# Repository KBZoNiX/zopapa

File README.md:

# Zopapa

A two-wheel differential-drive line-following robot: Arduino Nano firmware, an 8-channel reflectance sensor array, and two custom KiCad PCBs.

Full functional specification: [`docs/FSD.html`](docs/FSD.html) · User manual (Spanish): [`docs/MANUAL.html`](docs/MANUAL.html)

## Features

- PD line-following control loop (proportional + derivative, ~500 Hz)
- Relay-feedback (Åström–Hägglund) autotune — computes and installs new gains from an induced oscillation
- EEPROM persistence of tuned speed/gains and sensor calibration — no need to re-sweep the line sensor on every power-cycle
- Serial/Bluetooth command interface for live tuning and telemetry (shared UART, 9600 baud)
- Optional turbine/vacuum subsystem for extra downforce, ramped proportionally to steering correction
- On-board HMI: pushbutton (short press starts/stops; long press saves gains to EEPROM or recalibrates the sensor, depending on DIP 4 — see FSD §7.1), 4-position DIP bank, status LED, buzzer

## Repo layout

```
src/zopapa/       Arduino sketch (zopapa.ino is the entry point)
src/libraries/    Vendored first-party libraries: DRV8833 (motor driver), ATRSensors (line sensor)
hardware/         KiCad PCB projects — main_pcb (Rapiduino) and line_sensor_pcb (ATR-8A)
docs/FSD.html     Functional Specification Document
docs/MANUAL.html  User manual (Spanish) — physical controls and BT/Serial commands
```

## Build

Requires [arduino-cli](https://arduino.github.io/arduino-cli/) with the `arduino:avr` core installed.

```sh
arduino-cli compile --fqbn arduino:avr:nano --libraries src/libraries src/zopapa
```

Arduino IDE: open `src/zopapa/zopapa.ino` directly, and copy or symlink `src/libraries/*` into your sketchbook's `libraries/` folder first.

## Flash

Most Nano (and clone) boards need the old-bootloader CPU variant:

```sh
arduino-cli compile --fqbn arduino:avr:nano:cpu=atmega328old --libraries src/libraries -u -p /dev/ttyUSB0 src/zopapa
```

If uploads fail with repeated `not in sync` errors, that's this — try the `atmega328old` variant. Requires your account to be in the `dialout` group (Linux).

## Command interface

Sent over Serial or Bluetooth (same UART, 9600 baud):

| Command | Function | Example |
|---|---|---|
| `S` | Start | `S` |
| `P` | Stop | `P` |
| `T` | Run autotune | `T` |
| `Vxxx` | Set speed | `V180` |
| `Kxxx` | Set KP | `K22.5` |
| `Dxxx` | Set KD | `D15.3` |
| `R` | Read current parameters | `R` |
| `L` | Load parameters from EEPROM | `L` |
| `W` | Save parameters to EEPROM | `W` |
| `Q` | Live sensor bar test | `Q` |
| `C` | Force a fresh sensor calibration sweep, then save it | `C` |
| `H` | Help | `H` |

See [`docs/FSD.html`](docs/FSD.html) for the full electrical interconnect, BOM, control-loop math, and known quirks.

## Notes

- Firmware comments and Serial output are in Spanish.
- No test suite.

## License

[MIT](LICENSE), except `src/libraries/ATRSensors`, which retains the CC BY-SA 3.0 notice of the Pololu QTRSensors code it's derived from (see the file header).

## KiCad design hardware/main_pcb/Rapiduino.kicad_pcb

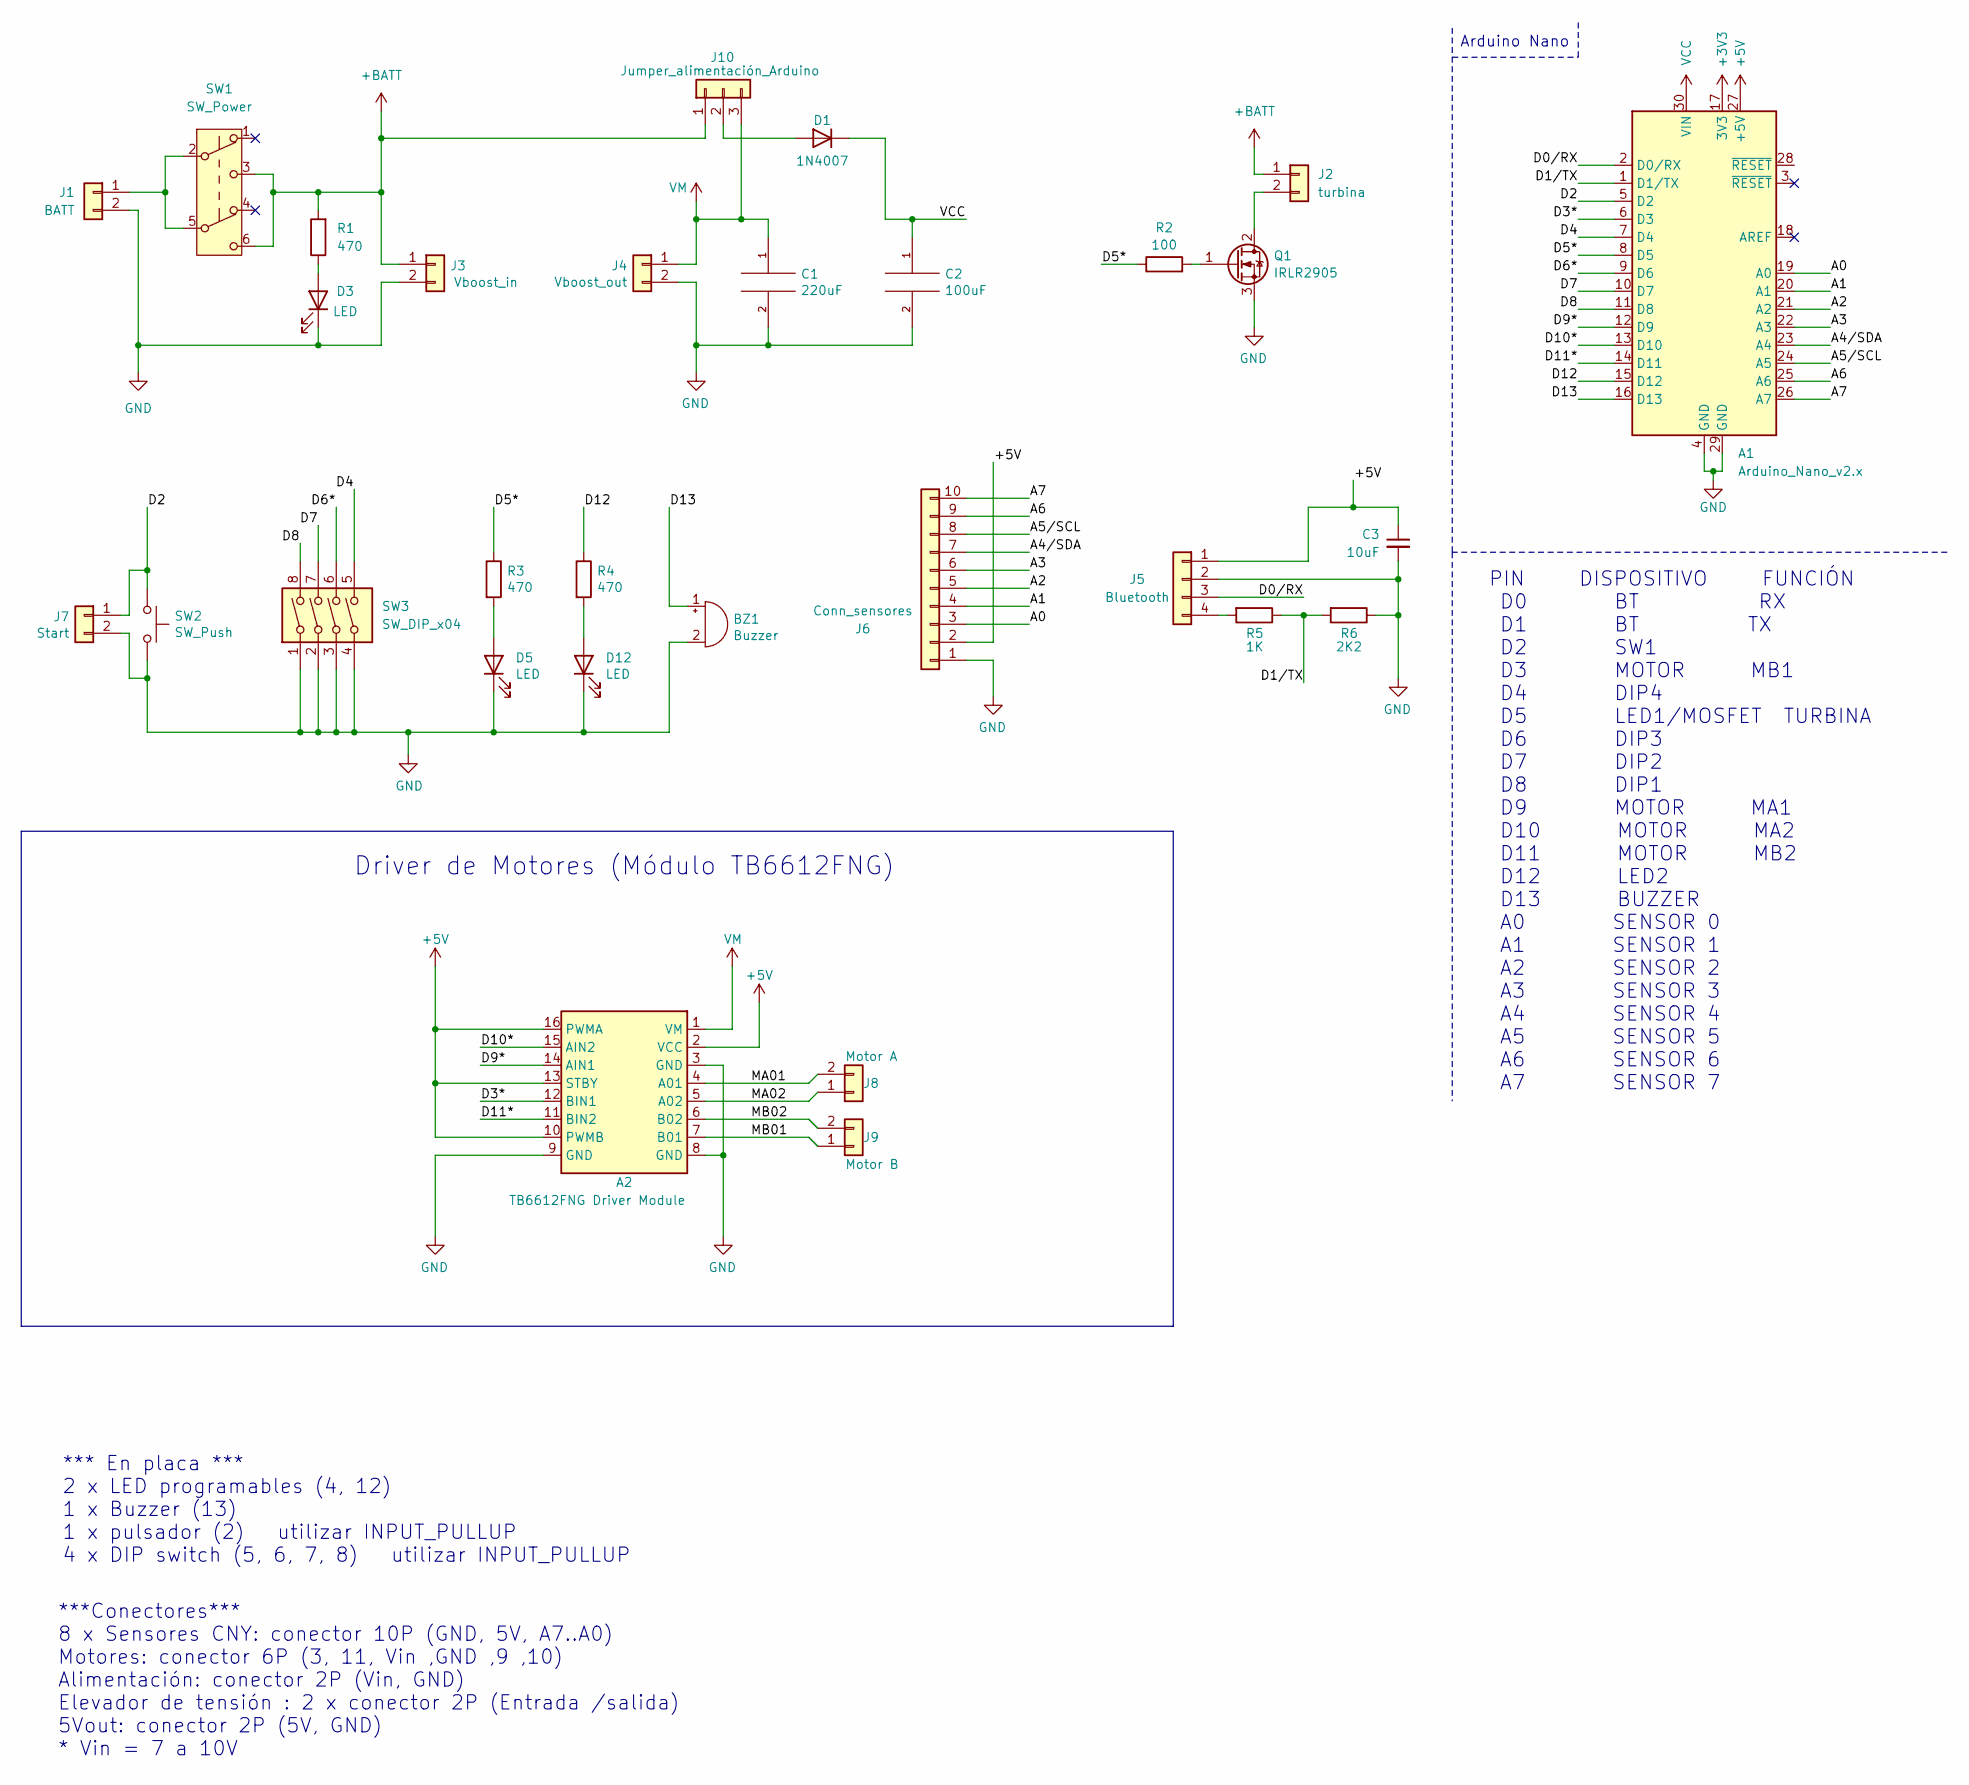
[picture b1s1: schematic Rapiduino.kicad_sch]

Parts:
A1: Arduino_Nano_v2.x; Arduino_Nano
A2: TB6612FNG Driver Module
BZ1: Buzzer; Buzzer_12x9.5RM7.6
C1: 220uF; CP_Radial_D6.3mm_P2.50mm
C2: 100uF; CP_Radial_D6.3mm_P2.50mm
C3: 10uF; C_1206_3216Metric_Pad1.33x1.80mm_HandSolder
D1: 1N4007; D_DO-41_SOD81_P7.62mm_Horizontal
D3, D5, D12: LED; LED_1206_3216Metric_Pad1.42x1.75mm_HandSolder
J1: BATT; PinHeader_1x02_P2.54mm_Vertical
J2: turbina; PinHeader_1x02_P2.54mm_Vertical
J3: Vboost_in; PinHeader_1x02_P2.54mm_Vertical
J4: Vboost_out; PinHeader_1x02_P2.54mm_Vertical
J5: Bluetooth; PinSocket_1x04_P2.54mm_Vertical
J6: Conn_sensores; PinHeader_1x10_P2.54mm_Vertical
J7: Start; PinHeader_1x02_P2.54mm_Vertical
J8: Motor A; PinHeader_1x02_P2.54mm_Vertical
J9: Motor B; PinHeader_1x02_P2.54mm_Vertical
J10: Jumper_alimentación_Arduino; PinHeader_1x03_P2.54mm_Vertical
Q1: IRLR2905; TO-252-2
R1, R3, R4: 470; R_0805_2012Metric_Pad1.20x1.40mm_HandSolder
R2: 100; R_0805_2012Metric_Pad1.20x1.40mm_HandSolder
R5: 1K; R_0805_2012Metric_Pad1.20x1.40mm_HandSolder
R6: 2K2; R_0805_2012Metric_Pad1.20x1.40mm_HandSolder
SW1: SW_Power; SW_Push_2P2T_Toggle_7x7mm
SW2: SW_Push; SW_PUSH_6mm
SW3: SW_DIP_x04; SW_DIP_SPSTx04_Slide_9.78x12.34mm_W7.62mm_P2.54mm

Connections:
+3V3: A1.17 (3V3)
+5V: A1.27 (+5V), A2.2 (VCC), A2.10 (PWMB), A2.13 (STBY), A2.16 (PWMA), C3.1, J5.1, J6.2
+BATT: J2.1, J3.1, J10.1, R1.2, SW1.3 (C), SW1.6 (C)
/A0: A1.19 (A0), J6.3
/A1: A1.20 (A1), J6.4
/A2: A1.21 (A2), J6.5
/A3: A1.22 (A3), J6.6
/A4/SDA: A1.23 (A4), J6.7
/A5/SCL: A1.24 (A5), J6.8
/A6: A1.25 (A6), J6.9
/A7: A1.26 (A7), J6.10
/D0/RX: A1.2 (D0/RX), J5.3
/D1/TX: A1.1 (D1/TX), R5.1, R6.2
/D2: A1.5 (D2), J7.1, SW2.1
/D3*: A1.6 (D3), A2.12 (BIN1)
/D4: A1.7 (D4), SW3.5
/D5*: A1.8 (D5), R2.1, R3.1
/D6*: A1.9 (D6), SW3.6
/D7: A1.10 (D7), SW3.7
/D8: A1.11 (D8), SW3.8
/D9*: A1.12 (D9), A2.14 (AIN1)
/D10*: A1.13 (D10), A2.15 (AIN2)
/D11*: A1.14 (D11), A2.11 (BIN2)
/D12: A1.15 (D12), R4.1
/D13: A1.16 (D13), BZ1.1 (-)
/MA01: A2.4 (A01), J8.2
/MA02: A2.5 (A02), J8.1
/MB01: A2.7 (B01), J9.1
/MB02: A2.6 (B02), J9.2
GND: A1.4 (GND), A1.29 (GND), A2.3 (GND), A2.8 (GND), A2.9 (GND), BZ1.2 (+), C1.2, C2.2, C3.2, D3.1 (K), D5.1 (K), D12.1 (K), J1.2, J3.2, J4.2, J5.2, J6.1, J7.2, Q1.3 (S), R6.1, SW2.2, SW3.1, SW3.2, SW3.3, SW3.4
unnamed: D1.2 (A), J10.2
unnamed: D3.2 (A), R1.1
unnamed: D5.2 (A), R3.2
unnamed: D12.2 (A), R4.2
unnamed: J1.1, SW1.2 (B), SW1.5 (B)
unnamed: J2.2, Q1.2 (D)
unnamed: J5.4, R5.2
unnamed: Q1.1 (G), R2.2
VCC: A1.30 (VIN), C2.1, D1.1 (K)
VM: A2.1 (VM), C1.1, J4.1, J10.3

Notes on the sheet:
*** En placa *** 2 x LED programables (4, 12) 1 x Buzzer (13) 1 x pulsador (2) utilizar INPUT_PULLUP 4 x DIP switch (5, 6, 7, 8) utilizar INPUT_PULLUP
Arduino Nano
Driver de Motores (Módulo TB6612FNG)
***Conectores*** 8 x Sensores CNY: conector 10P (GND, 5V, A7..A0) Motores: conector 6P (3, 11, Vin ,GND ,9 ,10) Alimentación: conector 2P (Vin, GND) Elevador de tensión : 2 x conector 2P (Entrada /salida) 5Vout: conector 2P (5V, GND) * Vin = 7 a 10V
PIN DISPOSITIVO FUNCIÓN D0 BT RX D1 BT TX D2 SW1 D3 MOTOR MB1 D4 DIP4 D5 LED1/MOSFET TURBINA D6 DIP3 D7 DIP2 D8 DIP1 D9 MOTOR MA1 D10 MOTOR MA2 D11 MOTOR MB2 D12 LED2 D13 BUZZER A0 SENSOR 0 A1 SENSOR 1 A2 SENSOR 2 A3 SENSOR 3 A4 SENSOR 4 A5 SENSOR 5 A6 SENSOR 6 A7 SENSOR 7

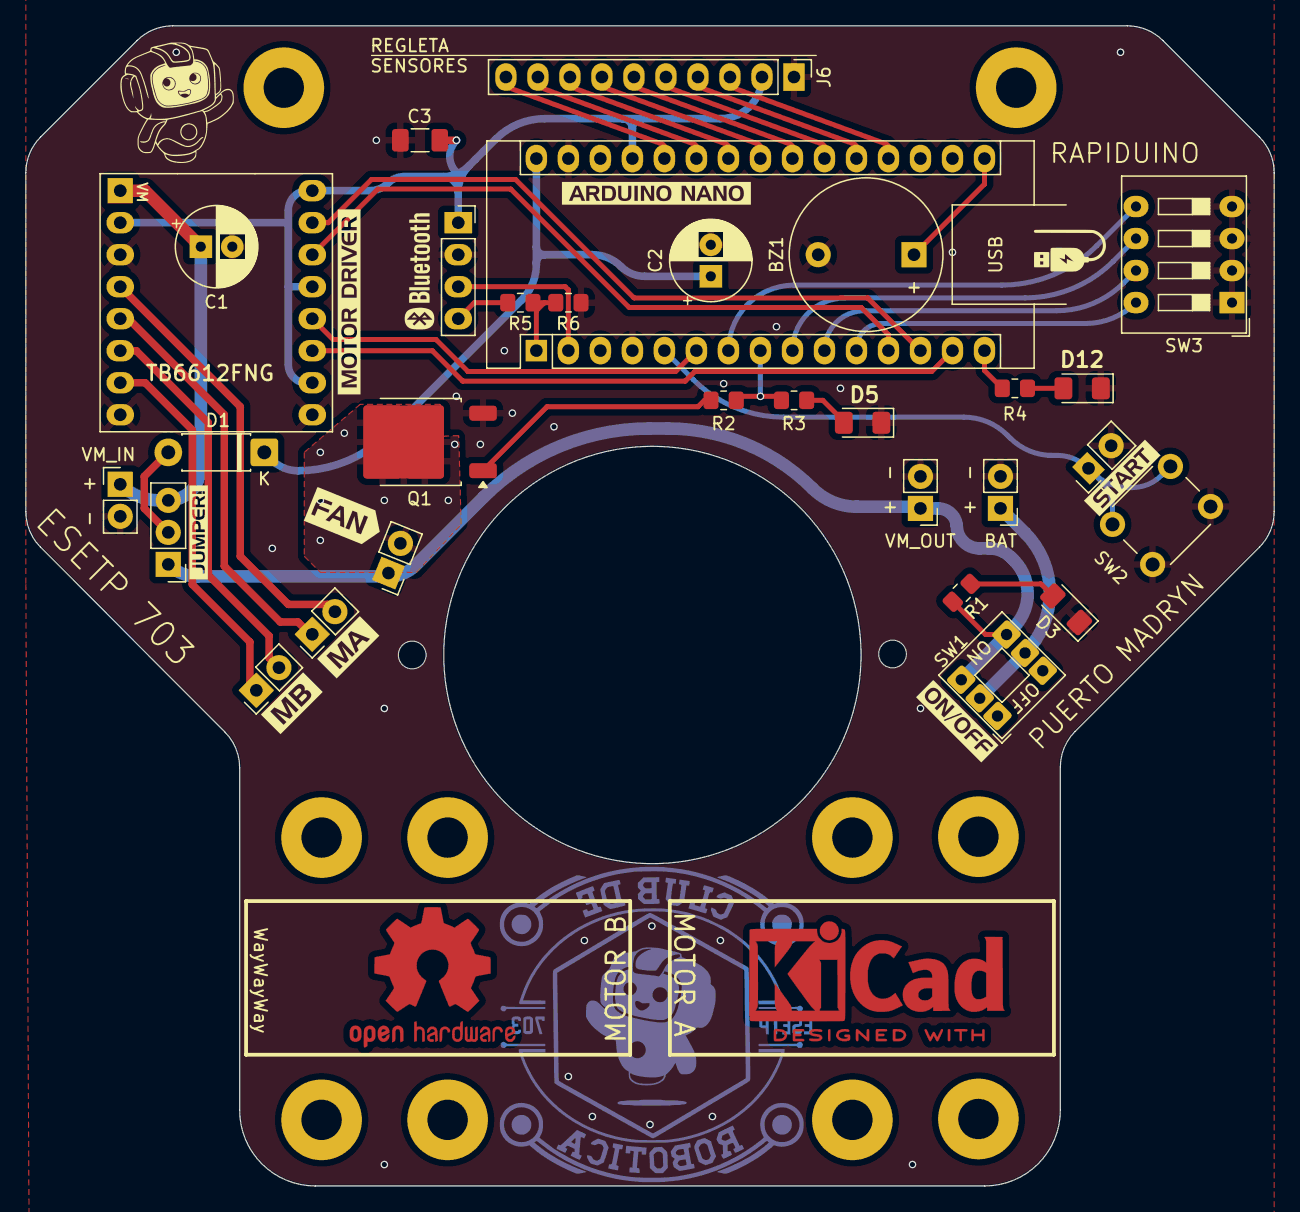
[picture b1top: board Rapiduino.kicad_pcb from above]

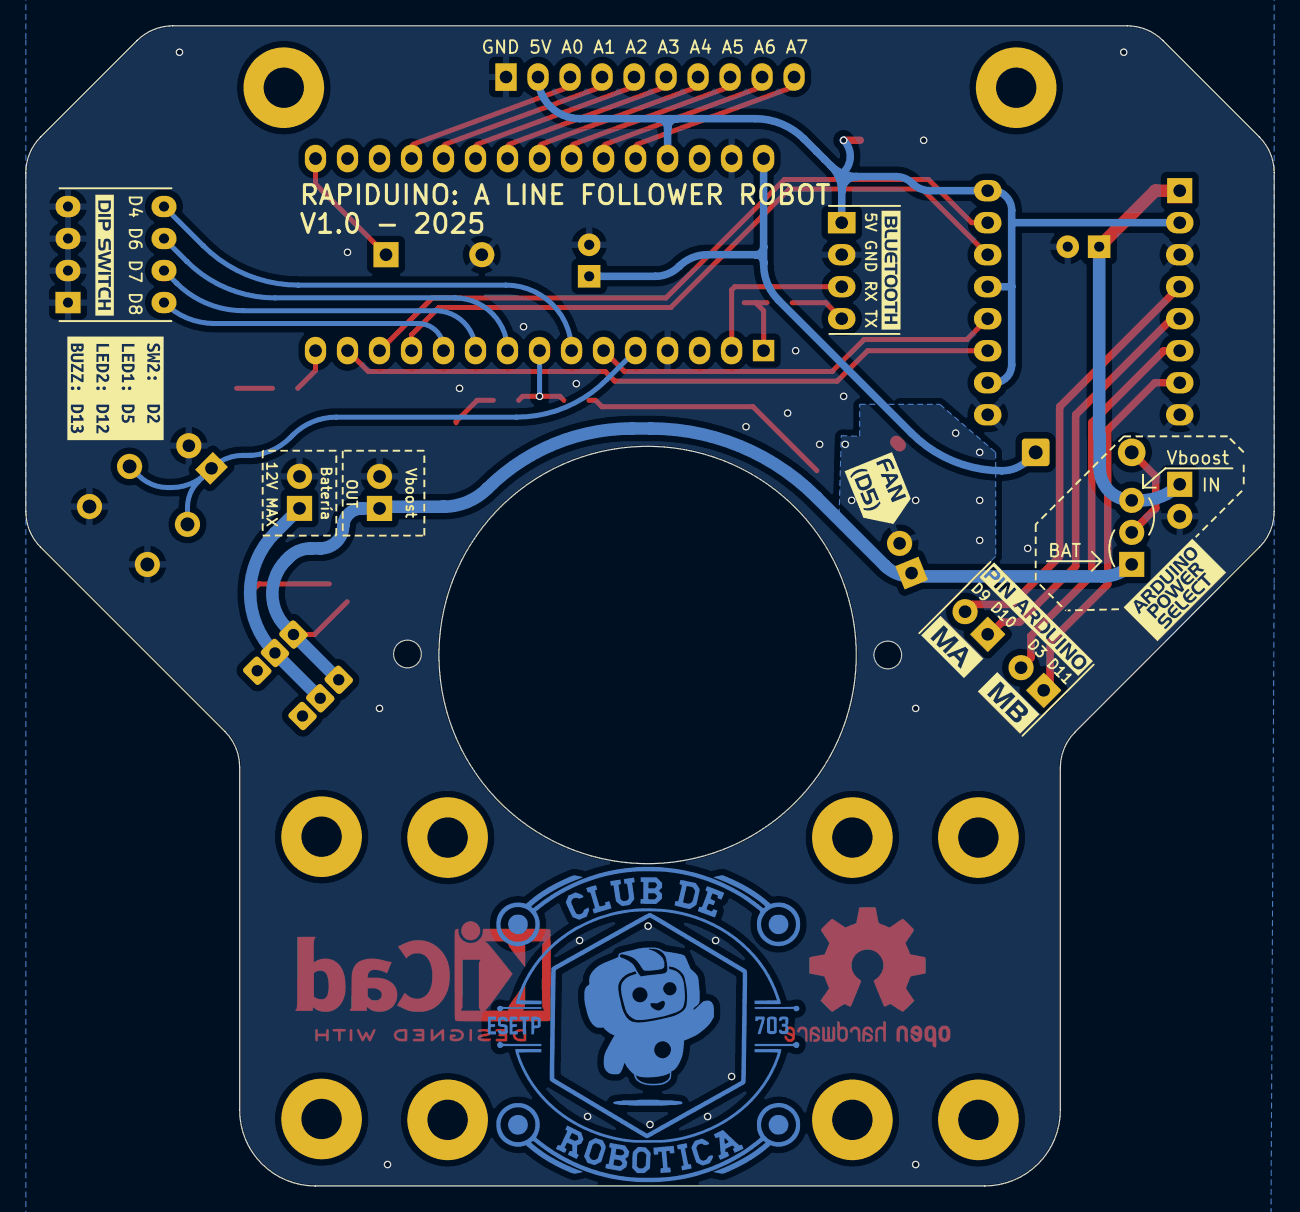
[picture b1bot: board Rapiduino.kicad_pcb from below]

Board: 2 copper layers, 99.1 x 92.1 mm, 46 parts (8 on the bottom side), 39 nets.

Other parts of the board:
kibuzzard-6850F7E0, kibuzzard-6850F7E0#2: G***; kibuzzard-6850F7E0
kibuzzard-6850F8CB: G***; kibuzzard-6850F8CB
kibuzzard-6850F811, kibuzzard-6850F811#2: G***; kibuzzard-6850F811
kibuzzard-6850FB1B: G***; kibuzzard-6850FB1B
kibuzzard-6850FB4B: G***; kibuzzard-6850FB4B
kibuzzard-68523F1B: G***; kibuzzard-68523F1B
kibuzzard-685101AF: G***; kibuzzard-685101AF
kibuzzard-685108A6: G***; kibuzzard-685108A6
kibuzzard-685108F3: G***; kibuzzard-685108F3
kibuzzard-685232D8: G***; kibuzzard-685232D8
kibuzzard-685241D4: G***; kibuzzard-685241D4
kibuzzard-685245CF: G***; kibuzzard-685245CF
kibuzzard-685246CF: G***; kibuzzard-685246CF
kibuzzard-6852314D: G***; kibuzzard-6852314D

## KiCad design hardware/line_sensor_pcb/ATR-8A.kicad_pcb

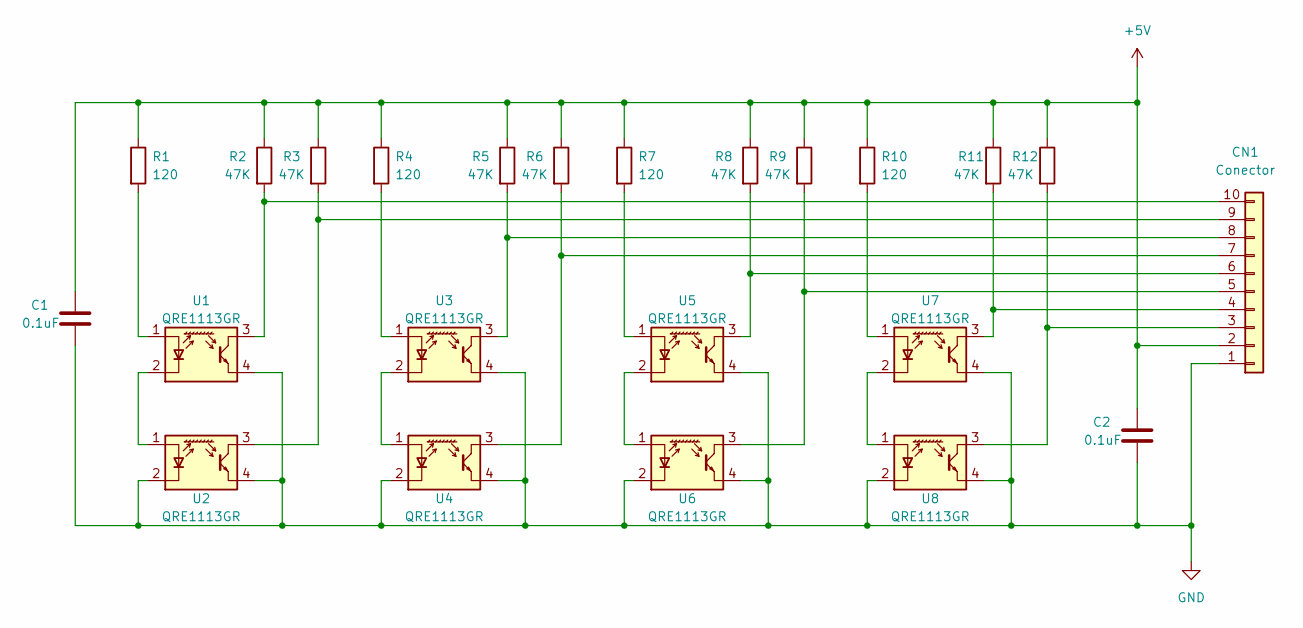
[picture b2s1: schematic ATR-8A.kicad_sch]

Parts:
C1, C2: 0.1uF; C_0805_2012Metric_Pad1.18x1.45mm_HandSolder
CN1: Conector; PinHeader_1x10_P2.54mm_Vertical
R1, R4, R7, R10: 120; R_0805_2012Metric_Pad1.20x1.40mm_HandSolder
R2, R3, R5, R6, R8, R9, R11, R12: 47K; R_0805_2012Metric_Pad1.20x1.40mm_HandSolder
U1, U2, U3, U4, U5, U6, U7, U8: QRE1113GR; OnSemi_CASE100CY

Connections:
+5V: C1.1, C2.1, CN1.2, R1.1, R2.1, R3.1, R4.1, R5.1, R6.1, R7.1, R8.1, R9.1, R10.1, R11.1, R12.1
GND: C1.2, C2.2, CN1.1, U1.4, U2.2 (K), U2.4, U3.4, U4.2 (K), U4.4, U5.4, U6.2 (K), U6.4, U7.4, U8.2 (K), U8.4
unnamed: CN1.3, R12.2, U8.3
unnamed: CN1.4, R11.2, U7.3
unnamed: CN1.5, R9.2, U6.3
unnamed: CN1.6, R8.2, U5.3
unnamed: CN1.7, R6.2, U4.3
unnamed: CN1.8, R5.2, U3.3
unnamed: CN1.9, R3.2, U2.3
unnamed: CN1.10, R2.2, U1.3
unnamed: R1.2, U1.1 (A)
unnamed: U1.2 (K), U2.1 (A)
unnamed: R4.2, U3.1 (A)
unnamed: U3.2 (K), U4.1 (A)
unnamed: R7.2, U5.1 (A)
unnamed: U5.2 (K), U6.1 (A)
unnamed: R10.2, U7.1 (A)
unnamed: U7.2 (K), U8.1 (A)

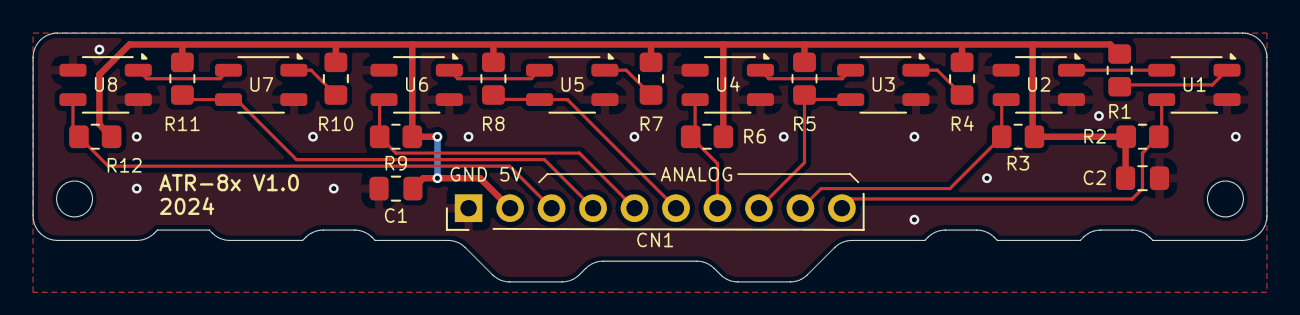
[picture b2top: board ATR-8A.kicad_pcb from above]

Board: 2 copper layers, 75.6 x 15.2 mm, 23 parts (0 on the bottom side), 18 nets.
